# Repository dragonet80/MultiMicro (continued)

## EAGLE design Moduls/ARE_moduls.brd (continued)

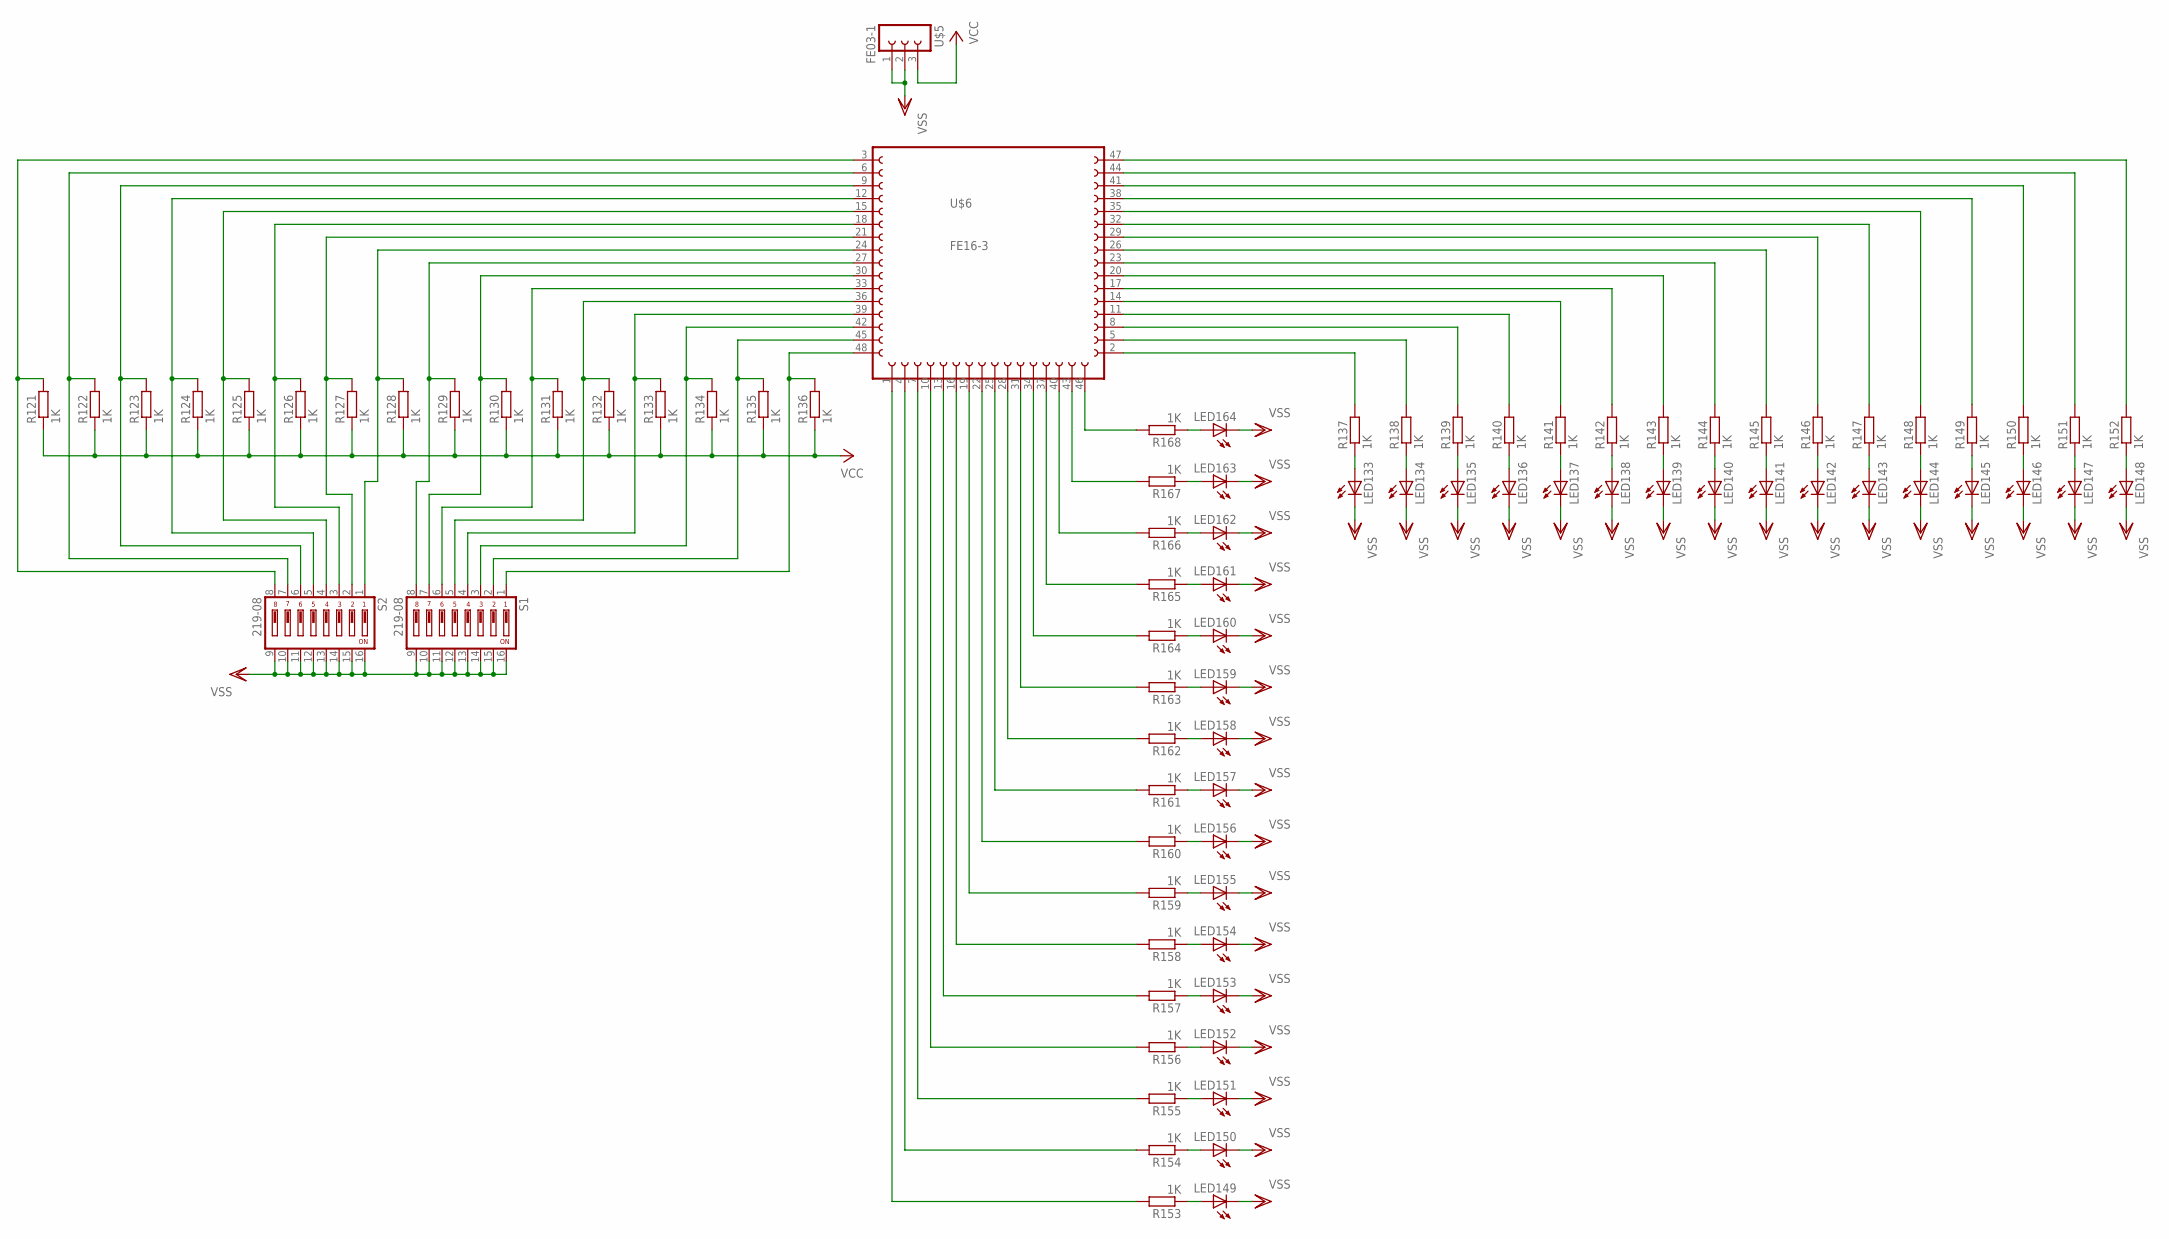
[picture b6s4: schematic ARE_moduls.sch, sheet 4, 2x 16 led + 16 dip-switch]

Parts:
LED133, LED134, LED135, LED136, LED137, LED138, LED139, LED140, LED141, LED142, LED143, LED144, LED145, LED146, LED147, LED148, LED149, LED150, LED151, LED152, LED153, LED154, LED155, LED156, LED157, LED158, LED159, LED160, LED161, LED162, LED163, LED164: LEDCHIPLED_0805; CHIPLED_0805
R121, R122, R123, R124, R125, R126, R127, R128, R129, R130, R131, R132, R133, R134, R135, R136, R137, R138, R139, R140, R141, R142, R143, R144, R145, R146, R147, R148, R149, R150, R151, R152, R153, R154, R155, R156, R157, R158, R159, R160, R161, R162, R163, R164, R165, R166, R167, R168: 1K; M0805
S1, S2: 219-08; CTS-219-08
U$5: FE03-1
U$6: FE16-3

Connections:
unnamed: R135.2, S1.2, U$6.45
unnamed: R136.2, S1.1, U$6.48
unnamed: R134.2, S1.3, U$6.42
unnamed: R133.2, S1.4, U$6.39
unnamed: R132.2, S1.5, U$6.36
unnamed: R131.2, S1.6, U$6.33
unnamed: R130.2, S1.7, U$6.30
unnamed: R129.2, S1.8, U$6.27
unnamed: R128.2, S2.1, U$6.24
unnamed: R127.2, S2.2, U$6.21
unnamed: R126.2, S2.3, U$6.18
unnamed: R125.2, S2.4, U$6.15
unnamed: R124.2, S2.5, U$6.12
unnamed: R123.2, S2.6, U$6.9
unnamed: R122.2, S2.7, U$6.6
unnamed: R121.2, S2.8, U$6.3
unnamed: LED133.A, R137.1
unnamed: LED134.A, R138.1
unnamed: LED135.A, R139.1
unnamed: LED136.A, R140.1
unnamed: LED137.A, R141.1
unnamed: LED138.A, R142.1
unnamed: LED139.A, R143.1
unnamed: LED140.A, R144.1
unnamed: LED141.A, R145.1
unnamed: LED142.A, R146.1
unnamed: LED143.A, R147.1
unnamed: LED144.A, R148.1
unnamed: LED145.A, R149.1
unnamed: LED146.A, R150.1
unnamed: LED147.A, R151.1
unnamed: LED148.A, R152.1
unnamed: R137.2, U$6.2
unnamed: R138.2, U$6.5
unnamed: R139.2, U$6.8
unnamed: R140.2, U$6.11
unnamed: R141.2, U$6.14
unnamed: R142.2, U$6.17
unnamed: R143.2, U$6.20
unnamed: R144.2, U$6.23
unnamed: R145.2, U$6.26
unnamed: R146.2, U$6.29
unnamed: R147.2, U$6.32
unnamed: R148.2, U$6.35
unnamed: R149.2, U$6.38
unnamed: R150.2, U$6.41
unnamed: R151.2, U$6.44
unnamed: R152.2, U$6.47
unnamed: LED149.A, R153.1
unnamed: LED150.A, R154.1
unnamed: LED151.A, R155.1
unnamed: LED152.A, R156.1
unnamed: LED153.A, R157.1
unnamed: LED154.A, R158.1
unnamed: LED155.A, R159.1
unnamed: LED156.A, R160.1
unnamed: LED157.A, R161.1
unnamed: LED158.A, R162.1
unnamed: LED159.A, R163.1
unnamed: LED160.A, R164.1
unnamed: LED161.A, R165.1
unnamed: LED162.A, R166.1
unnamed: LED163.A, R167.1
unnamed: LED164.A, R168.1
unnamed: R168.2, U$6.46
unnamed: R167.2, U$6.43
unnamed: R166.2, U$6.40
unnamed: R165.2, U$6.37
unnamed: R164.2, U$6.34
unnamed: R163.2, U$6.31
unnamed: R162.2, U$6.28
unnamed: R161.2, U$6.25
unnamed: R160.2, U$6.22
unnamed: R159.2, U$6.19
unnamed: R158.2, U$6.16
unnamed: R157.2, U$6.13
unnamed: R156.2, U$6.10
unnamed: R155.2, U$6.7
unnamed: R154.2, U$6.4
unnamed: R153.2, U$6.1
VCC: R121.1, R122.1, R123.1, R124.1, R125.1, R126.1, R127.1, R128.1, R129.1, R130.1, R131.1, R132.1, R133.1, R134.1, R135.1, R136.1, U$5.3; also elsewhere on the board
VSS: LED133.C, LED134.C, LED135.C, LED136.C, LED137.C, LED138.C, LED139.C, LED140.C, LED141.C, LED142.C, LED143.C, LED144.C, LED145.C, LED146.C, LED147.C, LED148.C, LED149.C, LED150.C, LED151.C, LED152.C, LED153.C, LED154.C, LED155.C, LED156.C, LED157.C, LED158.C, LED159.C, LED160.C, LED161.C, LED162.C, LED163.C, LED164.C, S1.9, S1.10, S1.11, S1.12, S1.13, S1.14, S1.15, S1.16, S2.9, S2.10, S2.11, S2.12, S2.13, S2.14, S2.15, S2.16, U$5.1, U$5.2; also elsewhere on the board

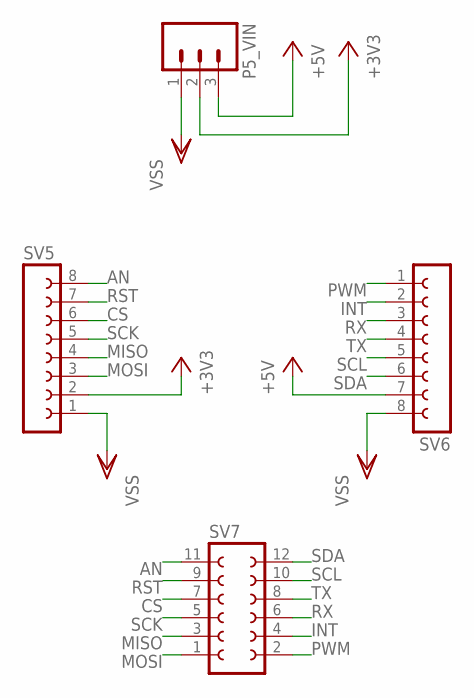
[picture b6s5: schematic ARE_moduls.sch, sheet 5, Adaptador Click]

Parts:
P5_VIN: M03PTH; 1X03
SV5, SV6: FE08-1; FE08
SV7: FE06-2

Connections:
+3V3: P5_VIN.2, SV5.2; also elsewhere on the board
+5V: P5_VIN.3, SV6.7; also elsewhere on the board
AN: SV5.8, SV7.11
CS: SV5.6, SV7.7
INT: SV6.2, SV7.4
MISO: SV5.4, SV7.3
MOSI: SV5.3, SV7.1
PWM: SV6.1, SV7.2
RST: SV5.7, SV7.9
RX: SV6.3, SV7.6
SCK: SV5.5, SV7.5
SCL: SV6.5, SV7.10
SDA: SV6.6, SV7.12
TX: SV6.4, SV7.8
VSS: P5_VIN.1, SV5.1, SV6.8; also elsewhere on the board

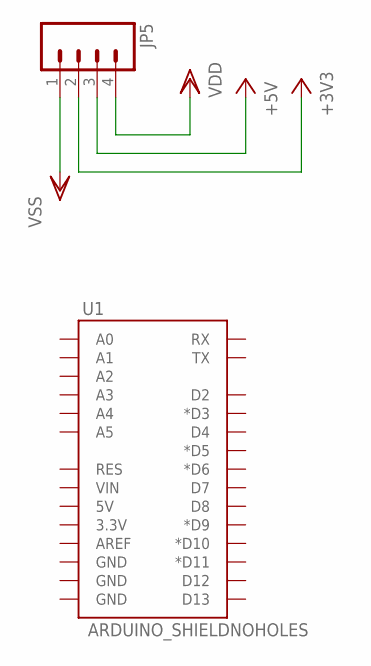
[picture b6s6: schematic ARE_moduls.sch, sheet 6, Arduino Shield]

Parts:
JP5: M04PTH; 1X04
U1: ARDUINO_SHIELDNOHOLES; DUEMILANOVE_SHIELD_NOHOLES

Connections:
+3V3: JP5.2; also elsewhere on the board
+5V: JP5.3; also elsewhere on the board
VDD: JP5.4
VSS: JP5.1; also elsewhere on the board

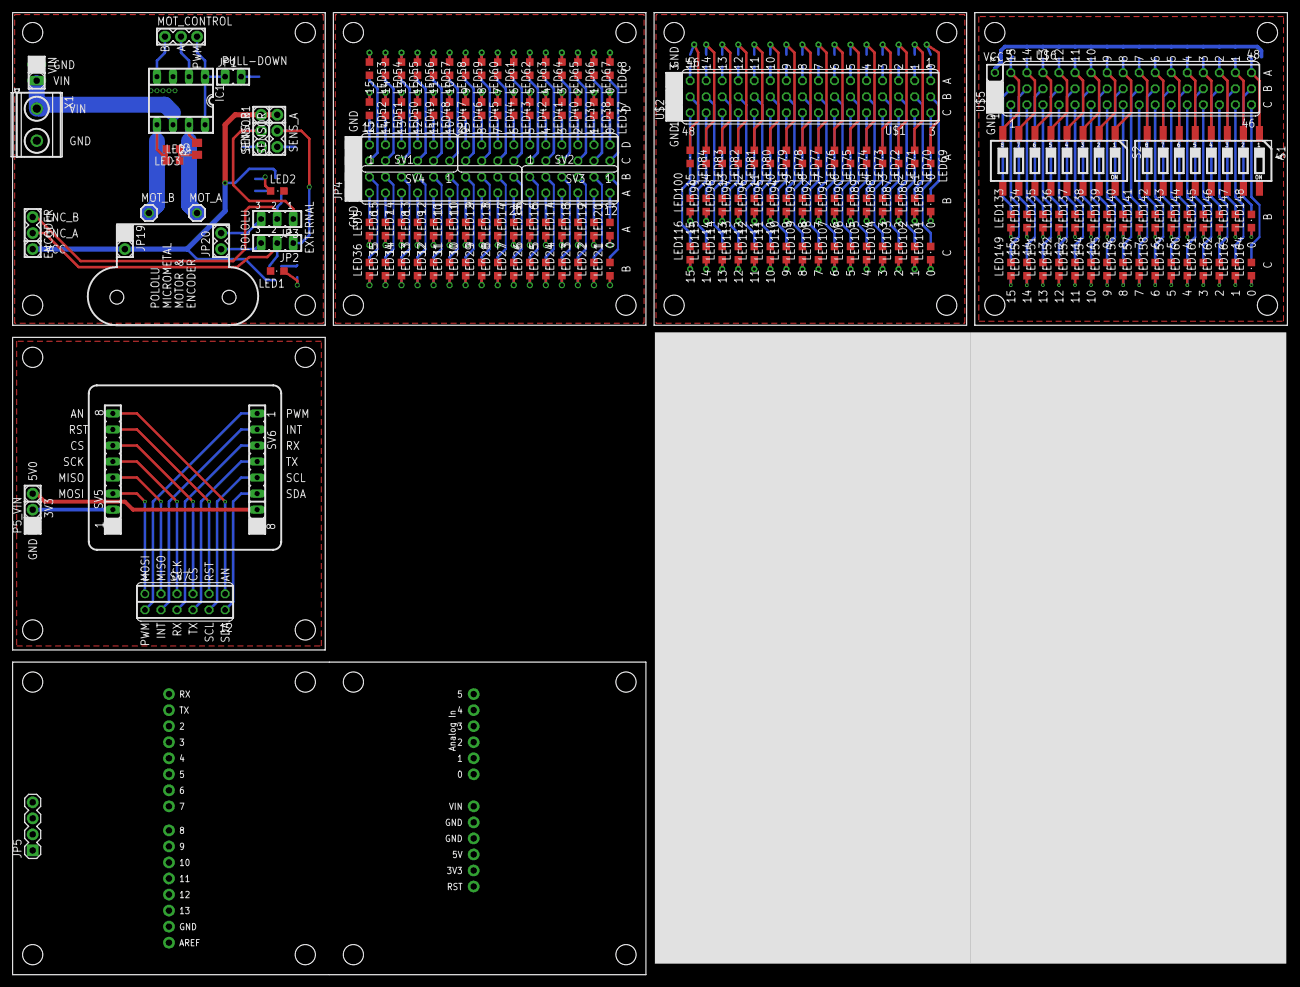
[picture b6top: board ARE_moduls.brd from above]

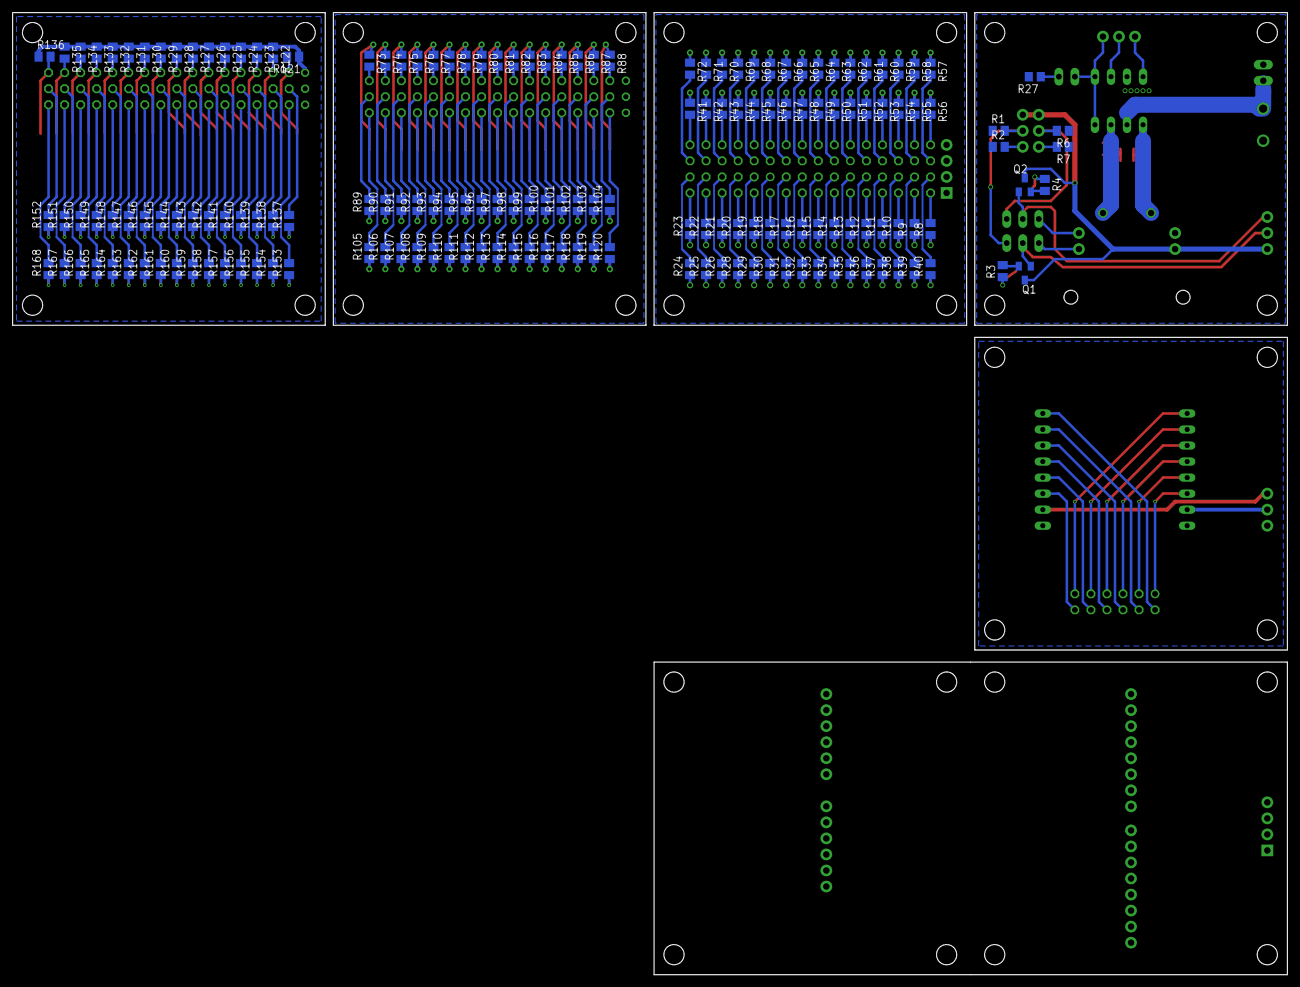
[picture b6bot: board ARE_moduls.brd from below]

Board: 2 copper layers, 201.9 x 152.4 mm, 349 parts (169 on the bottom side), 340 nets.
